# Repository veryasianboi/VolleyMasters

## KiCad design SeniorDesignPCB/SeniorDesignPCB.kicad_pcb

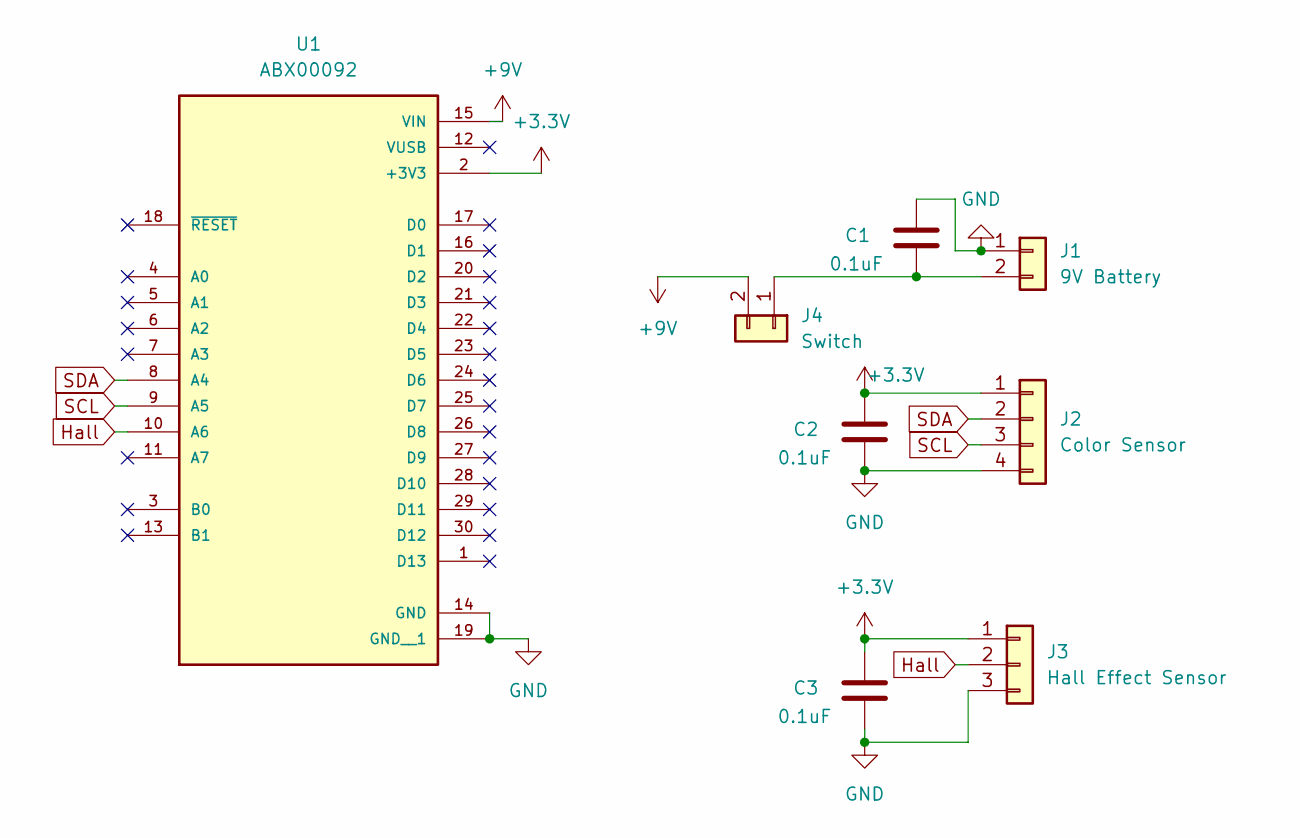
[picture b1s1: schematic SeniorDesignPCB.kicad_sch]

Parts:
C1, C2, C3: 0.1uF; C_0805_2012Metric_Pad1.18x1.45mm_HandSolder
J1: 9V Battery; PinHeader_1x02_P2.54mm_Vertical
J2: Color Sensor; PinHeader_1x04_P2.54mm_Vertical
J3: Hall Effect Sensor; PinHeader_1x03_P2.54mm_Vertical
J4: Switch; PinHeader_1x02_P2.54mm_Vertical
U1: ABX00092; Arduino_Nano; PARTREV 27/02/2024

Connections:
+3.3V: C2.1, C3.1, J2.1, J3.1, U1.2 (+3V3)
+9V: J4.2, U1.15 (VIN)
GND: C1.1, C2.2, C3.2, J1.1, J2.4, J3.3, U1.14 (GND), U1.19 (GND__1)
Hall: J3.2, U1.10 (A6)
unnamed: C1.2, J1.2, J4.1
SCL: J2.3, U1.9 (A5)
SDA: J2.2, U1.8 (A4)

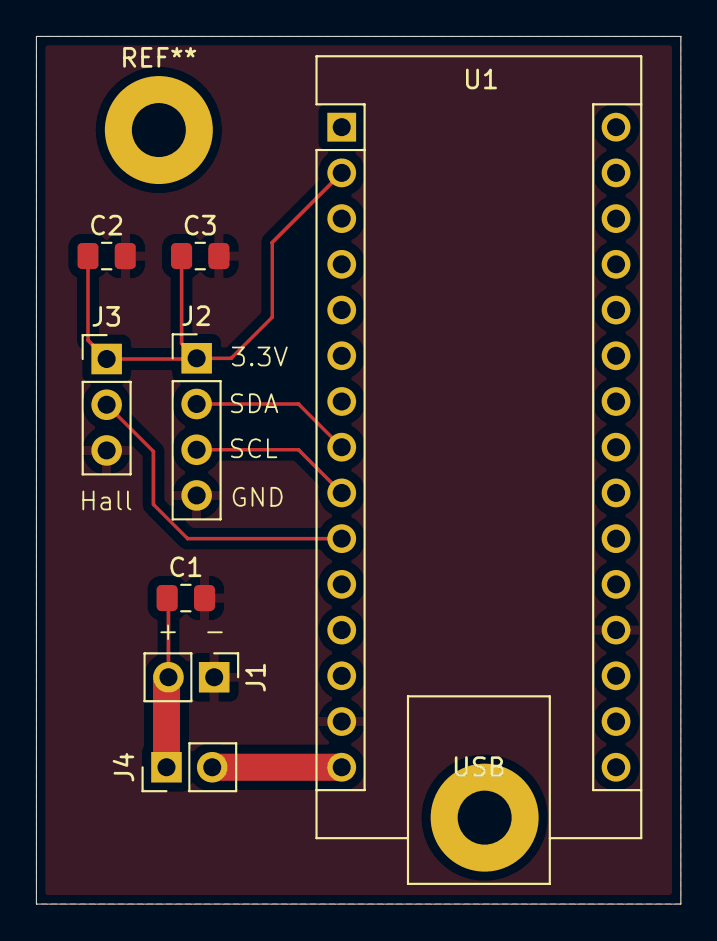
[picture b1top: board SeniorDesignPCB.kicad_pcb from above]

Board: 2 copper layers, 35.8 x 48.2 mm, 8 parts (0 on the bottom side), 7 nets.

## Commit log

2025-03-03 encoder code added
2025-03-05 imu code added
2025-04-06 bluetooth added
2025-04-07 changed data string output
2025-04-09 matlab bluetooth added
2025-04-14 strsplit functionality added
2025-04-14 color sensor
2025-04-22 everything
